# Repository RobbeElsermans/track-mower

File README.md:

# Track-Mower
A conceptual grass mower equipped with tracks for enhanced mobility.

## Overview
The Track-Mower is built around the ESP D1 Mini microcontroller, which provides WiFi, Bluetooth, and BLE capabilities. Communication between the driver and the mower is established via Bluetooth. Commands are sent as single characters, with each character corresponding to a specific action the mower will execute for a predefined duration.

## Features
- **Microcontroller**: ESP D1 Mini with WiFi, Bluetooth, and BLE.
- **Command-based Control**: Simple single-character commands for predefined actions.
- **Bluetooth Communication**: Reliable connection between the mower and a smartphone.

## How to Use
To operate the Track-Mower:
1. Install the [Serial Bluetooth Terminal](https://play.google.com/store/apps/details?id=de.kai_morich.serial_bluetooth_terminal) app on your Android device.
2. Pair your smartphone with the Track-Mower via Bluetooth.
3. Use the app to send commands to the mower.

## Command List
The following commands can be used to control the Track-Mower:

| Command | Action   | Duration  | Description                          |
|---------|----------|-----------|--------------------------------------|
| **F**   | Forward  | 1 second  | Moves the mower forward.             |
| **B**   | Backward | 1 second  | Moves the mower backward.            |
| **R**   | Right    | 0.5 second| Turns the mower to the right using both tracks. |
| **L**   | Left     | 0.5 second| Turns the mower to the left using both tracks.  |
| **M**   | Mower    | Gradual   | Spins up the blades gradually.       |

### Example Usage
To drive the mower forward for 2 seconds, turn left, and then start the blades:
```
F
F
L
M
```

## What to print
- 1x [Battery_assemblyBattery_holder](track-mower/CAD/3D_printing/tank_mower-Battery_assemblyBattery_holder.stl)
- 1x [chassis_body_V2](track-mower/CAD/3D_printing/tank_mower-chassis_body_V2.stl )
- 2x [Track_assemblybearing002](track-mower/CAD/3D_printing/tank_mower-Track_assemblybearing002.stl )
- 2x [Track_assemblybearing_holder_out001](track-mower/CAD/3D_printing/tank_mower-Track_assemblybearing_holder_out001.stl )
- 4x [Track_assemblybearing_holder_out_608002](track-mower/CAD/3D_printing/tank_mower-Track_assemblybearing_holder_out_608002.stl )
- 6x [Track_assemblyExtender](track-mower/CAD/3D_printing/tank_mower-Track_assemblyExtender.stl )
- 2x [Track_assemblyFollower](track-mower/CAD/3D_printing/tank_mower-Track_assemblyFollower.stl )
- 6x [Track_assemblyOverWheel](track-mower/CAD/3D_printing/tank_mower-Track_assemblyOverWheel.stl )
- 2x [Track_assemblyPuller001](track-mower/CAD/3D_printing/tank_mower-Track_assemblyPuller001.stl )
- 58x [Track_assemblytrack](track-mower/CAD/3D_printing/tank_mower-Track_assemblytrack.stl )
- 2x [Track_assemblyTrack_plate](track-mower/CAD/3D_printing/tank_mower-Track_assemblyTrack_plate.stl )
- 6x [Track_assemblyWasher](track-mower/CAD/3D_printing/tank_mower-Track_assemblyWasher.stl)
- 1x [Track_assemblyWasher](track-mower/CAD/3D_printing/Blade.stl)

## Other things
- 608ZZ bearings
- M3 washers, nuts and bolts
- Hot glue
- PowerPlus adapter
- DC motors
- Controller board

## Future Improvements
Here are some ideas for future enhancements:
1. **Advanced Controller**: Develop a controller for precise real-time control of the Track-Mower.
2. **PCB Redesign**: Improve the PCB design to provide more stable current sensing.
3. **Code Optimization**: Refactor the codebase and port it to an RTOS for better performance and scalability.

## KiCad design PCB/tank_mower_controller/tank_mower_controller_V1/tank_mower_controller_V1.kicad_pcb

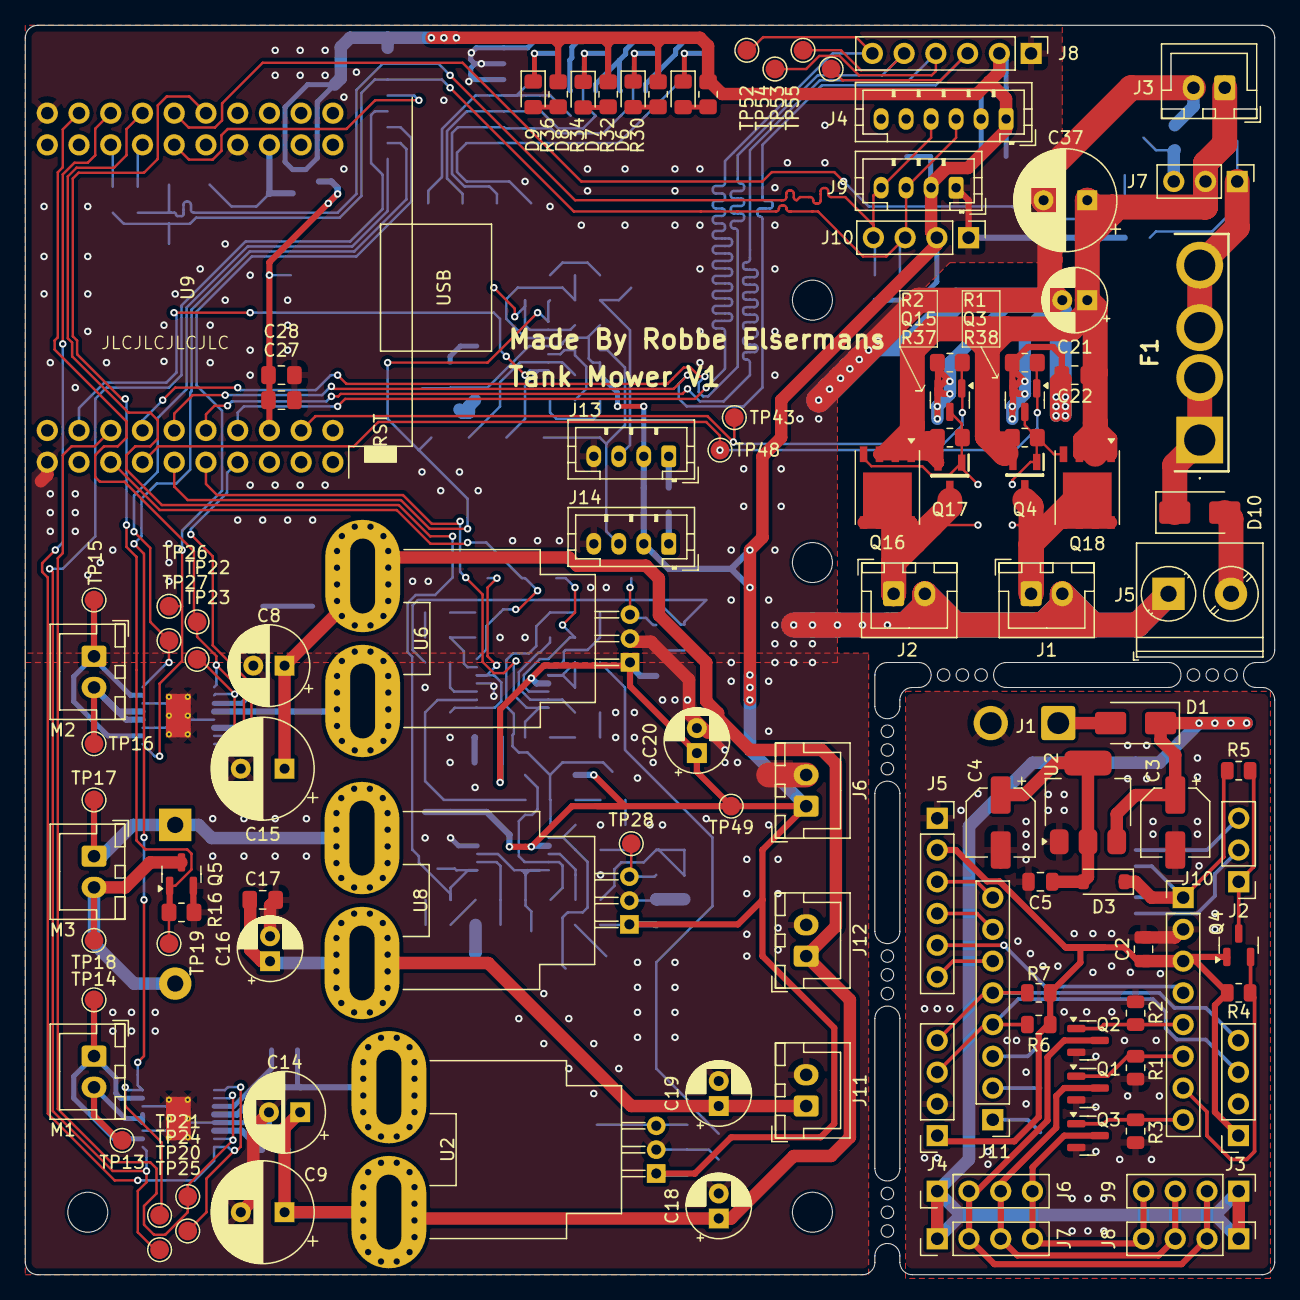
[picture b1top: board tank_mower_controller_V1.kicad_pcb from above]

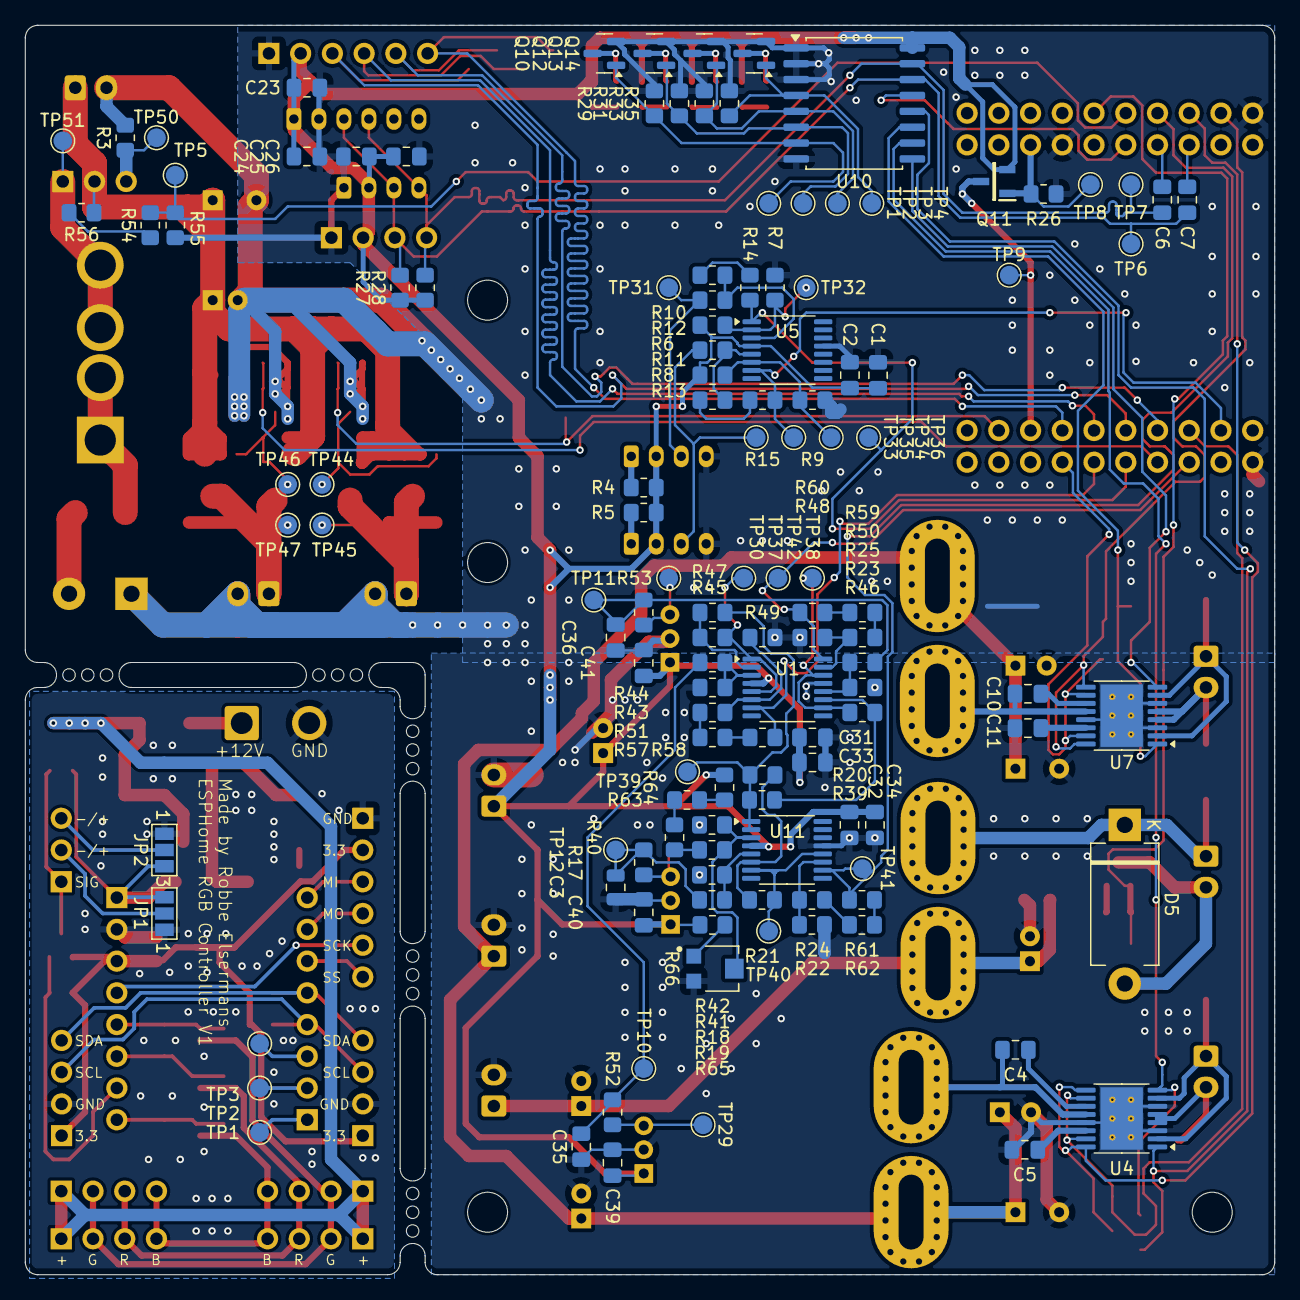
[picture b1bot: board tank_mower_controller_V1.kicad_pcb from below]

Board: 2 copper layers, 100.0 x 100.0 mm, 237 parts (128 on the bottom side), 106 nets.

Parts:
C1, C4#2, C6, C7, C10, C24, C26, C28, C31, C32: 10n; C_0805_2012Metric_Pad1.18x1.45mm_HandSolder
C2: 10µ; C_0805_2012Metric
C2#2, C17, C22, C23, C25, C27, C33, C34, C39, C40, C41: 10µ; C_0805_2012Metric_Pad1.18x1.45mm_HandSolder
C3, C4: 10µ; CP_Elec_5x5.4
C3#2: 1µ; C_0805_2012Metric
C5: 10n; C_0805_2012Metric
C5#2, C11: 2.2µ; C_0805_2012Metric_Pad1.18x1.45mm_HandSolder
C8, C14: 100µ; CP_Radial_D6.3mm_P2.50mm
C9, C15: 407µ; CP_Radial_D8.0mm_P3.50mm
C16, C18, C19, C20, C21: 10µ; CP_Radial_D5.0mm_P2.00mm
C35, C36: 1µ; C_0805_2012Metric_Pad1.18x1.45mm_HandSolder
C37: 470µ; CP_Radial_D8.0mm_P3.50mm
D1: 1N4009; D_SMA
D3: 1N4819; D_SOD-123
D5: D; D_DO-201_P12.70mm_Horizontal
D6, D7, D8, D9: LED; LED_0805_2012Metric_Pad1.15x1.40mm_HandSolder
D10: D_Schottky; D_SMA
F1: MCCQ-121; MCCQ121
J1, J2, J3: LM2596_modul_in; JST_XH_B2B-XH-A_1x02_P2.50mm_Vertical
J1#2: Jack-DC; SolderWire-1sqmm_1x02_P5.4mm_D1.4mm_OD2.7mm
J2#2: IR-receiver; PinHeader_1x03_P2.54mm_Vertical
J3#2: I2C_expansion; PinSocket_1x04_P2.54mm_Vertical
J4: BMP280_Module; JST_PH_B6B-PH-K_1x06_P2.00mm_Vertical
J4#2: AHT10_module; PinSocket_1x04_P2.54mm_Vertical
J5: BMS_input; TerminalBlock_Phoenix_PT-1,5-2-5.0-H_1x02_P5.00mm_Horizontal
J5#2: SPI_expansion; PinSocket_1x06_P2.54mm_Vertical
J6, J11, J12: LM2596_modul_out; JST_XH_B2B-XH-A_1x02_P2.50mm_Vertical
J6#2, J7#2, J8, J9#2: Conn_01x04; PinHeader_1x04_P2.54mm_Vertical
J7: On/Off_toggle; PinHeader_1x03_P2.54mm_Vertical
J8#2: SPI_Connector; PinHeader_1x06_P2.54mm_Vertical
J9: SSD1306; JST_PH_B4B-PH-K_1x04_P2.00mm_Vertical
J10, J11#2: Conn_01x08; PinHeader_1x08_P2.54mm_Vertical
J10#2: I2C_Extender; PinHeader_1x04_P2.54mm_Vertical
J13, J14: GP1S094HCZ0F; JST_PH_B4B-PH-K_1x04_P2.00mm_Vertical
JP1, JP2: Jumper_3_Open; SolderJumper-3_P1.3mm_Open_Pad1.0x1.5mm_NumberLabels
M1, M2, M3: Motor_DC; JST_XH_B2B-XH-A_1x02_P2.50mm_Vertical
Q1, Q2, Q3, Q4: AO3400A; SOT-23
Q3#2, Q10, Q12, Q13, Q14, Q15: 2N7002; SOT-23
Q4#2, Q11, Q17: SI2323; SOT95P237X112-3N
Q5: IRLML6244; SOT-23
Q16, Q18: Si7141DP; PowerPAK_SO-8_Single
R1, R2, R16, R22, R48, R49, R58, R60, R62: 10k; R_0805_2012Metric_Pad1.20x1.40mm_HandSolder
R1#2, R2#2, R3: 100k; R_0805_2012Metric
R3#2, R6#2, R7#2, R8, R9, R18, R19, R20, R21, R23, R25, R37, R38, R39, R41, R42, R43, R44, R45, R46, R47, R55: 1M; R_0805_2012Metric_Pad1.20x1.40mm_HandSolder
R4, R5: 10k; R_0805_2012Metric
R4#2, R5#2, R30, R32, R34, R36: 120; R_0805_2012Metric_Pad1.20x1.40mm_HandSolder
R6, R7: 4k7; R_0805_2012Metric
R10, R11, R12, R13, R14, R15, R40, R63: 100k; R_0805_2012Metric_Pad1.20x1.40mm_HandSolder
R17, R52, R53: 3.3k; R_0805_2012Metric_Pad1.20x1.40mm_HandSolder
R24, R50, R51: 68k; R_0805_2012Metric_Pad1.20x1.40mm_HandSolder
R26: R; R_0805_2012Metric_Pad1.20x1.40mm_HandSolder
R27, R28: 4k7; R_0805_2012Metric_Pad1.20x1.40mm_HandSolder
R29, R31, R33, R35: 10M; R_0805_2012Metric_Pad1.20x1.40mm_HandSolder
R54: 2.2M; R_0805_2012Metric_Pad1.20x1.40mm_HandSolder
R56: 3.3M; R_0805_2012Metric_Pad1.20x1.40mm_HandSolder
R57, R59, R61: 12k; R_0805_2012Metric_Pad1.20x1.40mm_HandSolder
R64, R65: 15k; R_0805_2012Metric_Pad1.20x1.40mm_HandSolder
R66: 1M; TRIM_TC33X-2-105E
TP1, TP1#2, TP2, TP2#2, TP3, TP3#2, TP4, TP5, TP6, TP7, TP8, TP9, TP10, TP11, TP12, TP13, TP14, TP15, TP16, TP17, TP18, TP19, TP20, TP21, TP22, TP23, TP24, TP25, TP26, TP27, TP28, TP29, TP30, TP31, TP32, TP33, TP34, TP35, TP36, TP37, TP38, TP39, TP40, TP41, TP42, TP43, TP44, TP45, TP46, TP47, TP48, TP49, TP50, TP51, TP52, TP53, TP54, TP55: TestPoint; TestPoint_Pad_D1.5mm
U1, U5, U11: TLV2775AIN; TSSOP-16_4.4x5mm_P0.65mm
U2, U6, U8: ACS758xCB-050B-PFF; Allegro_CB_PFF
U2#2: AMS1117-5.0; SOT-223-3_TabPin2
U4, U7: DRV8833PWP; HTSSOP-16-1EP_4.4x5mm_P0.65mm_EP3.4x5mm_Mask2.46x2.31mm_The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
U9: esp32-wemos-d1-mini
U10: PCF8574; SOIC-16W_7.5x10.3mm_P1.27mm

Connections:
+BATT: C21.1, C22.1, C37.1, J3.1, J7.2, Q4#2.2 (S), Q16.1 (S), Q16.2 (S), Q16.3 (S), Q17.2 (S), Q18.1 (S), Q18.2 (S), Q18.3 (S), R37.1, R38.1, R56.1
/motor_control/current_signal_converter/1_minus: R45.2, R47.1, U1.2 (1IN-)
/motor_control/current_signal_converter/1_out: R47.2, TP37.1, U1.1 (1OUT), U1.5 (2IN+)
/motor_control/current_signal_converter/1_plus: R43.2, R44.2, U1.3 (1IN+)
/motor_control/current_signal_converter/2_minus: R49.1, R51.1, U1.6 (2IN-)
/motor_control/current_signal_converter/3_minus: R39.2, R46.1, U1.11 (3IN-)
/motor_control/current_signal_converter/3_out: R46.2, TP38.1, U1.10 (3OUT), U1.14 (4IN+)
/motor_control/current_signal_converter/3_plus: R23.2, R25.2, U1.12 (3IN+)
/motor_control/current_signal_converter/4_minus: R48.1, R50.1, U1.15 (4IN-)
/motor_control/current_signal_converter/5_minus: R20.1, R39.1, R45.1, TP39.1, U11.1 (1OUT), U11.2 (1IN-)
/motor_control/current_signal_converter/5_plus: R41.2, R42.1, R66.2, U11.3 (1IN+)
/motor_control/current_signal_converter/6_minus: R20.2, R21.1, U11.6 (2IN-)
/motor_control/current_signal_converter/6_out: R21.2, TP40.1, U11.7 (2OUT), U11.12 (3IN+)
/motor_control/current_signal_converter/6_plus: R18.2, R19.2, U11.5 (2IN+)
/motor_control/current_signal_converter/7_minus: R22.1, R24.1, U11.11 (3IN-)
/motor_control/current_signal_converter/RAM_CURRENT_MOWER: C3#2.1, R17.2, R19.1, TP12.1
/motor_control/current_signal_converter/RAW_CURRENT_TRACK_1: C35.1, R44.1, R52.2, TP10.1
/motor_control/current_signal_converter/RAW_CURRENT_TRACK_2: C36.1, R25.1, R53.2, TP11.1
/motor_control/encoder/1_minus: R6#2.2, R7#2.1, TP32.1, U5.2 (1IN-)
/motor_control/encoder/1_plus: R10.2, R12.1, U5.3 (1IN+)
/motor_control/encoder/2_minus: R8.2, R9.1, TP34.1, U5.6 (2IN-)
/motor_control/encoder/2_plus: R11.2, R13.1, U5.5 (2IN+)
BATTERY_VOLTAGE_SCALED: R54.2, R55.1, TP5.1, U9.30 (IO_12/TDI)
BMS_VCC: F1.3, F1.4, J7.1, TP51.1
DISPLAY_SCL: C7.1, J4.3, J9.3, J10#2.3, R27.2, TP6.1, U10.14 (SCL)
DISPLAY_SDA: C6.1, J4.4, J9.4, J10#2.4, R28.2, TP7.1, U10.15 (SDA)
ENCODER_1: R14.2, TP36.1, U5.1 (1OUT), U9.9 (IO_33)
ENCODER_2: R15.2, TP35.1, U5.7 (2OUT), U9.4 (IO_36/SVP/A0)
GND: C1.2, C2.2, C2#2.2, C3.2, C3#2.2, C4.2, C5.2, C5#2.1, C8.2, C9.2, C11.1, C14.2, C15.2, C16.2, C17.2, C18.2, C19.2, C20.2, C21.2, C22.2, C23.2, C24.2, C25.2, C26.2, C27.2, C28.2, C31.2, C32.2, C33.2, C34.2, C35.2, C36.2, C37.2, C39.2, C40.2, C41.2, J1.2, J1#2.2, J2.2, J3.2, J3#2.2, J4.2, J4#2.2, J5.1, J5#2.1, J6.2, J8#2.1, J9.1, J10.2, J10#2.1, J11.2, J12.2, J13.4, J14.4, JP1.1 (A), JP2.1 (A), Q1.2 (S), Q2.2 (S), Q3.2 (S), Q3#2.2 (S), Q5.2 (S), Q10.2 (S), Q12.2 (S), Q13.2 (S), Q14.2 (S), Q15.2 (S), R1.2, R1#2.2, R2.2, R2#2.2, R3.2, R3#2.1, R7#2.2, R9.2, R16.2, R18.1, R22.2, R23.1, R26.2, R29.2, R31.2, R33.2, R35.2, R42.2, R43.1, R48.2, R49.2, R55.2, R66.3, U1.13 (GND), U2.2 (GND), U2#2.1 (GND), U4.3 (AISEN), U4.6 (BISEN), U4.13 (GND), U4.17 (GND), U5.13 (GND), U6.2 (GND), U7.3 (AISEN), U7.6 (BISEN), U7.13 (GND), U7.17 (GND), U8.2 (GND), U9.1 (GND), U9.22 (GND), U9.33 (GND), U10.1 (A0), U10.2 (A1), U10.3 (A2), U10.8 (VSS), U11.13 (GND)
IO-EXTENDER_INTERUPT: U9.29 (IO_17/D3), U10.13 (~INT)
LED_1: Q10.1 (G), R29.1, TP1#2.1, U10.7 (P3)
LED_2: Q12.1 (G), R31.1, TP2.1, U10.6 (P2)
LED_3: Q13.1 (G), R33.1, TP3.1, U10.5 (P1)
LED_4: Q14.1 (G), R35.1, TP4.1, U10.4 (P0)
MISO: J8#2.3, TP55.1, U9.10 (IO_19/D6)
MOSI: J8#2.4, TP54.1, U9.12 (IO_23/D7)
MOTOR_MOWER_CURRENT: R62.2, TP41.1, U9.28 (IO_32), U11.10 (3OUT)
MOTOR_MOWER_EN: Q5.1 (G), R16.1, TP19.1, U9.32 (IO_04)
MOTOR_TRACK_1_1: TP20.1, U4.9 (BIN1), U4.16 (AIN1), U9.26 (IO_25)
MOTOR_TRACK_1_2: TP21.1, U4.10 (BIN2), U4.15 (AIN2), U9.6 (IO_26/D0)
MOTOR_TRACK_1_CURRENT: R58.2, U1.7 (2OUT), U9.11 (IO_34)
MOTOR_TRACK_1_EN: TP25.1, U4.1 (~SLEEP), U10.12 (P7)
MOTOR_TRACK_1_FAULT: TP24.1, U4.8 (~FAULT), U10.10 (P5)
MOTOR_TRACK_2_1: TP22.1, U7.9 (BIN1), U7.16 (AIN1), U9.24 (IO_27)
MOTOR_TRACK_2_2: TP23.1, U7.10 (BIN2), U7.15 (AIN2), U9.13 (IO_14/TMS)
MOTOR_TRACK_2_CURRENT: R60.2, TP42.1, U1.16 (4OUT), U9.5 (IO_39/SVN)
MOTOR_TRACK_2_EN: TP26.1, U7.1 (~SLEEP), U10.11 (P6)
MOTOR_TRACK_2_FAULT: TP27.1, U7.8 (~FAULT), U10.9 (P4)
unnamed: D5.2 (A), M3.2 (-), Q5.3 (D), TP18.1
unnamed: D5.1 (K), M3.1 (+), TP17.1, U8.4 (IP+)
unnamed: D6.2 (A), R30.2
unnamed: D6.1 (K), Q10.3 (D)
unnamed: D7.2 (A), R32.2
unnamed: D7.1 (K), Q12.3 (D)
unnamed: D8.2 (A), R34.2
unnamed: D8.1 (K), Q13.3 (D)
unnamed: D9.2 (A), R36.2
unnamed: D9.1 (K), Q14.3 (D)
unnamed: D10.2 (A), J5.2
unnamed: D10.1 (K), F1.1, F1.2
unnamed: J1.1, Q4#2.3 (D), Q18.5 (D), TP47.1
unnamed: J2.1, J2#2.1, Q4.3 (D), Q16.5 (D), Q17.3 (D), R5.2, TP45.1
unnamed: J7.3, R3#2.2, TP50.1
unnamed: J13.1, R4#2.1
unnamed: J13.3, R10.1, TP31.1
unnamed: J14.1, R5#2.1
unnamed: J14.3, R11.1, TP33.1
unnamed: M1.1 (+), TP14.1, U4.2 (AOUT1), U4.7 (BOUT1)
unnamed: M1.2 (-), TP13.1, U4.4 (AOUT2), U4.5 (BOUT2)
unnamed: M2.1 (+), TP15.1, U7.2 (AOUT1), U7.7 (BOUT1)
unnamed: M2.2 (-), TP16.1, U7.4 (AOUT2), U7.5 (BOUT2)
unnamed: C27.1, C28.1, Q11.3 (D), TP9.1, U9.16 (3V3)
unnamed: Q11.1 (G), R26.1, TP8.1, U9.35 (VCC_(USB))
unnamed: Q15.3 (D), Q16.4 (G), Q17.1 (G), R37.2, TP44.1
unnamed: Q3#2.3 (D), Q4#2.1 (G), Q18.4 (G), R38.2, TP46.1
unnamed: R12.2, R14.1
unnamed: R13.2, R15.1
unnamed: R24.2, R61.1
unnamed: R40.1, R63.2
unnamed: R40.2, R41.1
unnamed: R50.2, R59.1
unnamed: R51.2, R57.1
unnamed: R54.1, R56.2
unnamed: R57.2, R58.1
unnamed: R59.2, R60.1
unnamed: R61.2, R62.1
unnamed: R63.1, R64.2
unnamed: R65.2, R66.1
unnamed: C4#2.2, U2.4 (IP+), U4.12 (VM)
unnamed: R52.1, TP29.1, U2.3 (VIOUT)
unnamed: C4#2.1, U4.11 (VCP)
unnamed: C5#2.2, U4.14 (VINT)
unnamed: C10.2, U6.5 (IP-), U7.12 (VM)
unnamed: R53.1, TP30.1, U6.3 (VIOUT)
unnamed: C10.1, U7.11 (VCP)
unnamed: C11.2, U7.14 (VINT)
unnamed: R17.1, TP28.1, U8.3 (VIOUT)
unnamed: C6.2, U9.27 (IO_21/D2/SDA)
unnamed: C7.2, U9.25 (IO_22/D1/SCL)
SCK: J8#2.5, TP53.1, U9.8 (IO_18/D5)
SS: J8#2.6, TP52.1, U9.14 (IO_05/D8)
VCC: C1.1, C2.1, C2#2.1, C20.1, C23.1, C24.1, C25.1, C26.1, C31.1, C32.1, C33.1, C34.1, C39.1, C40.1, C41.1, J3#2.1, J4.1, J4#2.1, J5#2.2, J6.1, J8#2.2, J9.2, J10.3, J10#2.2, J13.2, J14.2, Q4.1 (G), Q11.2 (S), R4.1, R4#2.2, R5#2.2, R6.1, R6#2.1, R7.1, R8.1, R27.1, R28.1, R30.1, R32.1, R34.1, R36.1, R64.1, R65.1, TP49.1, U1.4 (VDD), U2.1 (VCC), U5.4 (VDD), U6.1 (VCC), U8.1 (VCC), U10.16 (VDD), U11.4 (VDD)
VCC_MOTOR_MOWER: C16.1, C17.1, C19.1, J11.1, U8.5 (IP-)
VCC_MOTOR_MOWER_EN: Q3#2.1 (G), R1.1, TP48.1, U9.7 (IO_35)
VCC_MOTOR_TRACK: C8.1, C9.1, C14.1, C15.1, C18.1, J12.1, U2.5 (IP-), U6.4 (IP+)
VCC_MOTOR_TRACK_EN: Q15.1 (G), R2.1, TP43.1, U9.18 (IO_13/TCK)

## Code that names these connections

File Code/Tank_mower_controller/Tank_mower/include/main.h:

#ifndef MAIN_H
#define MAIN_H

#include <stdbool.h>
#include <stdint.h>

//Define pinouts
#define IO_EXTENDER_INTERUPT 17

#define SS 5
#define SCK 18
#define MISO 19
#define MOSI 23

#define VCC_MOTOR_TRACK_EN 13
//#define VCC_MOTOR_MOWER_EN 35  //Not working
// #define VCC_MOTOR_TRACK_EN 33
// #define VCC_MOTOR_MOWER_EN 36

//#define ENCODER_1 33
//#define ENCODER_2 36

#define BATTERY_VOLTAGE_SCALED 35//12
#define MOTOR_CURRENT_MOWER 32
#define MOTOR_TRACK_1_CURRENT 34
#define MOTOR_TRACK_2_CURRENT 39

#define MOTOR_TRACK_1_1 25
#define MOTOR_TRACK_1_2 26

#define MOTOR_TRACK_2_1 27
#define MOTOR_TRACK_2_2 14
#define MOTOR_MOWER_EN 4
#define MOTOR_TRACK_1_FAULT P5
#define MOTOR_TRACK_2_FAULT P4
#define MOTOR_TRACK_1_EN P7
#define MOTOR_TRACK_2_EN P6

#define LED_1 P3
#define LED_2 P2
#define LED_3 P1
#define LED_4 P0

void readCommand();
void calculateCurrent(uint8_t pin, float* current);
void calculateVoltage(uint8_t pin, float* voltage);
void displayData();
void handleCommand();
void executeCommand();
void setBool(uint8_t *bool_carrier, uint8_t bool_place);

void clearBool(uint8_t *bool_carrier, uint8_t bool_place);

uint8_t checkBool(uint8_t *bool_carrier, uint8_t bool_place);

#endif

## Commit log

2024-12-01 Add all content
2024-12-01 Add docs folder
2024-12-13 Add readme and edit portfolio
2024-12-13 Update files
2024-12-17 Cleanup + add content to readme
